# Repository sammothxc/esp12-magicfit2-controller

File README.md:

Using an ESP12F to add Wifi control to a Magic Fit 2 Vibration Exercise Plate

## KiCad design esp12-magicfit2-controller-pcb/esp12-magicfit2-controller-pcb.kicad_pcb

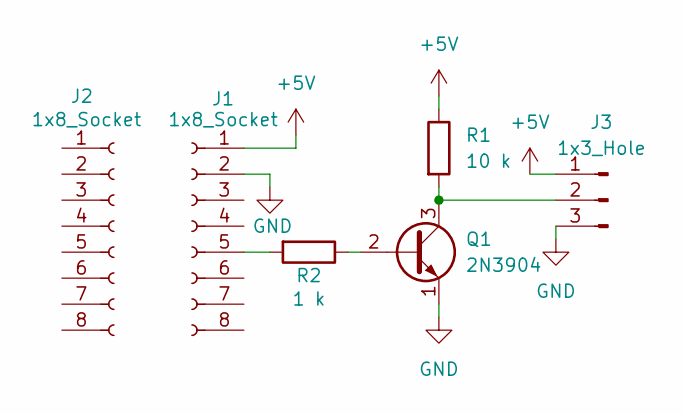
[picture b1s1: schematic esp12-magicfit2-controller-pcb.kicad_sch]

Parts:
J1, J2: 1x8_Socket; PinSocket_1x08_P2.54mm_Vertical
J3: 1x3_Hole; TO-3P-3_Vertical
Q1: 2N3904; PinHeader_1x03_P2.54mm_Vertical
R1: 10 k; R_Axial_DIN0207_L6.3mm_D2.5mm_P10.16mm_Horizontal
R2: 1 k; R_Axial_DIN0207_L6.3mm_D2.5mm_P10.16mm_Horizontal

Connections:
+5V: J1.1, J3.1, R1.1
GND: J1.2, J3.3, Q1.1 (E)
unnamed: J1.5, R2.2
unnamed: J3.2, Q1.3 (C), R1.2
unnamed: Q1.2 (B), R2.1

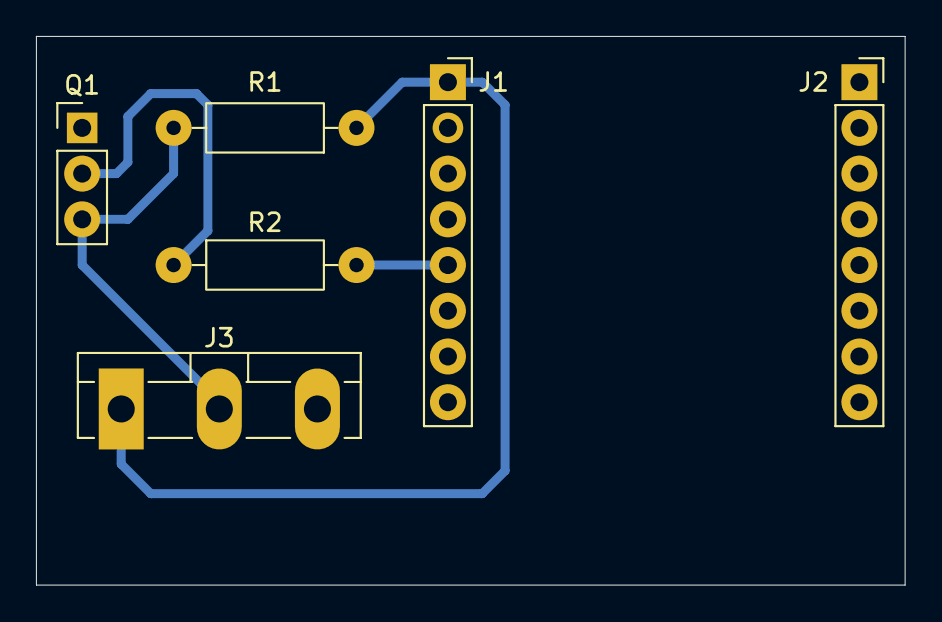
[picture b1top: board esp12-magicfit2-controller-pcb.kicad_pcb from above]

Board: 2 copper layers, 48.3 x 30.5 mm, 6 parts (0 on the bottom side), 5 nets.

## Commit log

2025-09-19 Initial commit: ESP8266 vibration plate controller
    Add .gitignore for secrets, GPLv3 license, bitbanged PWM Arduino sketch, and ESP8266-based MagicFit2 vibration plate controller with web UI for speed and timer control.
2025-09-19 Remove bitbanged PWM sketch and add OTA to controller
    Deleted the bitbanged-pwm.ino test file. Enhanced esp12-magicfit2-controller.ino by adding ArduinoOTA support for over-the-air updates, improved WiFi connection handling, and refactored setup for bet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
2025-09-19 Remove ArduinoOTA support and related code
    Eliminated all ArduinoOTA functionality, including password handling and OTA event callbacks. The code now uses mDNS for hostname resolution and simplifies the WiFi setup process.
2025-09-19 Add persistent workout plan support and UI overhaul
    Introduces a new persistent controller variant with workout plan support, including step sequencing, pause/resume, and progress tracking. The web UI is significantly enhanced with tabbed navigation, 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
2025-09-19 Rename persistent controller to BETA version
    Renamed esp12-magicfit2-controller_persistent.ino to esp12-magicfit2-controller_BETA.ino to reflect the new version or development status.
2025-09-19 Add screen wake lock to prevent sleep during workout
    Introduces a wake lock feature using the Screen Wake Lock API to keep the device screen on during workout plans. Includes a fallback for older iOS devices using a silent looping video, and ensures th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
2025-09-21 Add initial KiCad PCB design and fabrication files
    Added Gerber, drill, CNC, and project files for the esp12-magicfit2-controller PCB, including backups and fabrication outputs. This commit introduces the full set of files required for PCB manufactur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
2025-09-21 Update PCB project and CNC G-code files
2025-09-27 Update PCB CNC G-code and project files
    Reduced XY feedrate from 120 to 60 mm/min and Z cut depth from -0.04 to -0.05 mm in the PCB CNC G-code. Updated project and backup files, and removed a stale lock file.
2025-09-27 Refactor project structure to PlatformIO and update main functionality
    - Removed old controller code from esp12-magicfit2-controller_BETA.ino.
    - Added new main.cpp file with updated logic for controlling the vibration plate.
    - Introduced ElegantOTA for over-the-air updates.
    - Created README files for include, lib, and test directories to provide documentation.
    - Updated platformio.ini with necessary dependencies and configurations.
    - Enhanced HTML interface for better user interaction with the vibration plate.
2025-09-27 Add WiFi configuration management and web server setup
2025-09-27 Update access point SSID to match project name
2025-09-27 Update form action in WiFi configuration page to use correct endpoint
2025-09-27 Refactor PWM control logic and improve motor duty cycle management
2025-09-27 ramp up motor
2025-09-27 ramp down motor
2025-09-27 type issue with volatile int
2025-09-27 inverted duty logic clarifications
2025-09-27 ditto
2025-09-27 prevent jumps when changing speed mid ramp
2025-09-27 remove mdns because it dont work
2025-09-27 hostname
2025-11-08 more pcb
